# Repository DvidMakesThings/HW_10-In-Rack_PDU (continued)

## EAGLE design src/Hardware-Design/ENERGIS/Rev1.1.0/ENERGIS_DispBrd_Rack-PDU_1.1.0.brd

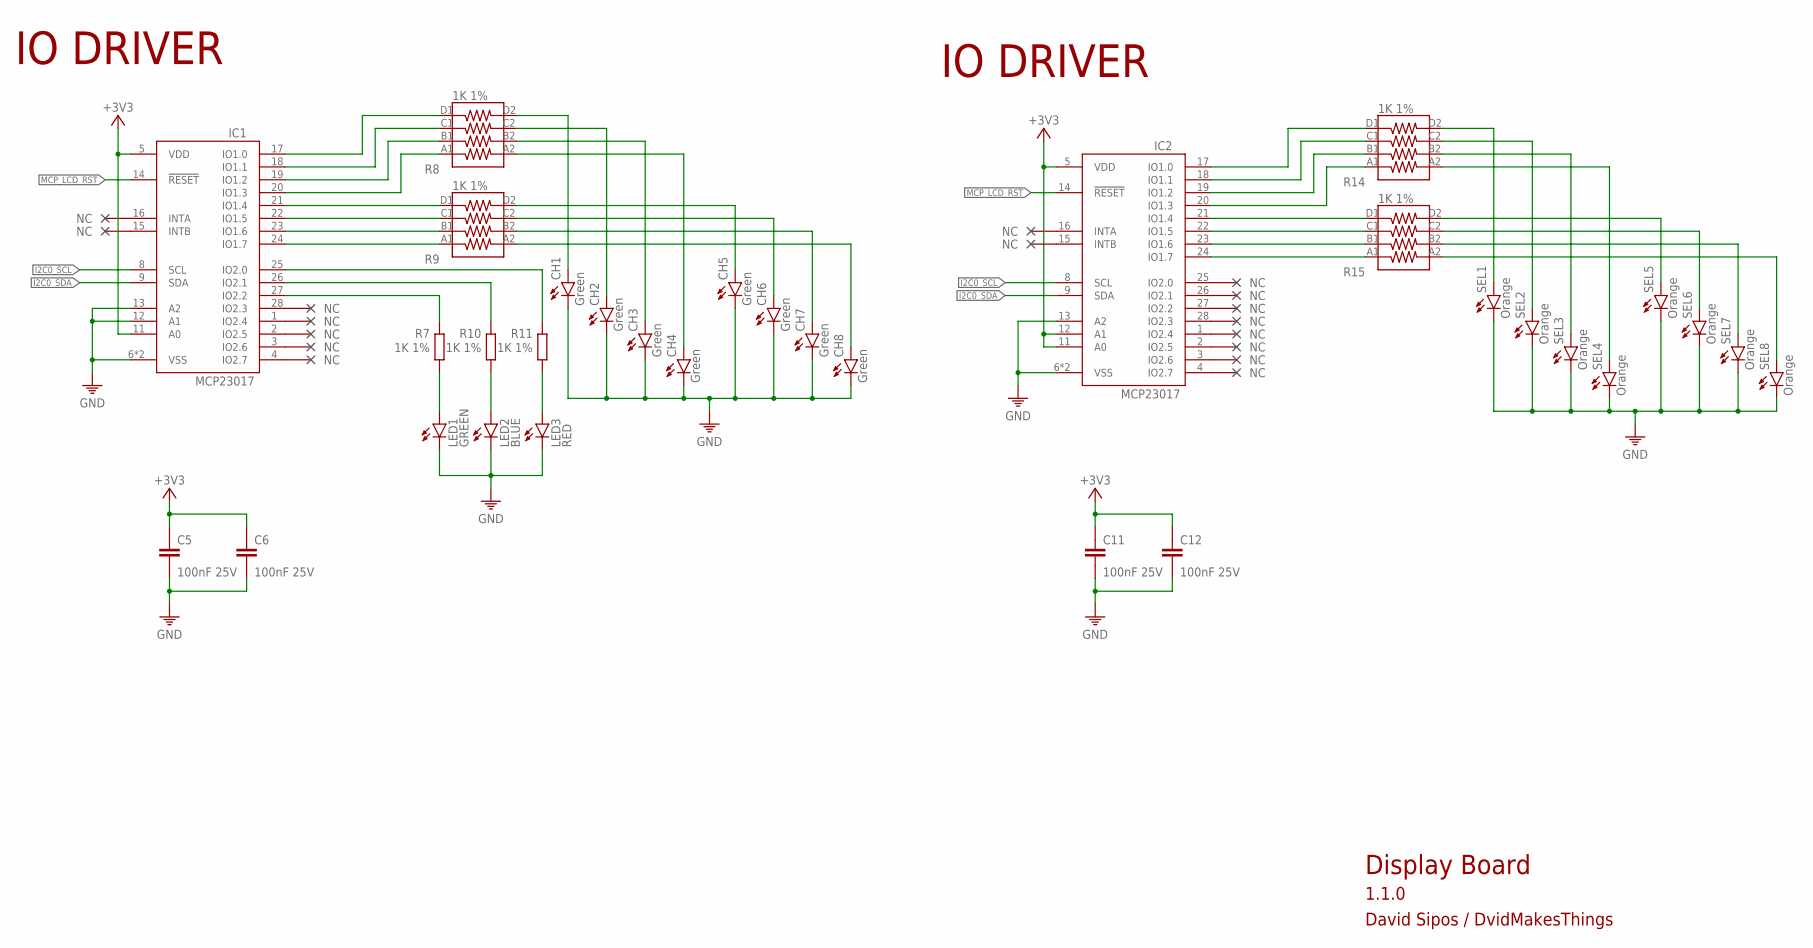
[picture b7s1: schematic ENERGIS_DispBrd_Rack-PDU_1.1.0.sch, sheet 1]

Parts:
C5, C6, C11, C12: 100nF 25V; 0402
CH1, CH2, CH3, CH4, CH5, CH6, CH7, CH8: Green; LED-0805
IC1, IC2: MCP23017T-E/ML; QFN28[6X6]ML
LED1: GREEN; LED3MM
LED2: BLUE; LED3MM
LED3: RED; LED3MM
R7, R10, R11: 1K 1%; 0402
R8, R9, R14, R15: 1K 1%; _0603X4-1206
SEL1, SEL2, SEL3, SEL4, SEL5, SEL6, SEL7, SEL8: Orange; LED-0805

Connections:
+3V3: C5.1, C6.1, C11.1, C12.1, IC1.5 (VDD), IC1.11 (A0), IC2.5 (VDD), IC2.11 (A0), IC2.12 (A1); also elsewhere on the board
GND: C5.2, C6.2, C11.2, C12.2, CH1.C, CH2.C, CH3.C, CH4.C, CH5.C, CH6.C, CH7.C, CH8.C, IC1.6 (VSS), IC1.12 (A1), IC1.13 (A2), IC1.PAD (VSS), IC2.6 (VSS), IC2.13 (A2), IC2.PAD (VSS), LED1.K (C), LED2.K (C), LED3.K (C), SEL1.C, SEL2.C, SEL3.C, SEL4.C, SEL5.C, SEL6.C, SEL7.C, SEL8.C; also elsewhere on the board
I2C0_SCL: IC1.8 (SCL), IC2.8 (SCL); also elsewhere on the board
I2C0_SDA: IC1.9 (SDA), IC2.9 (SDA); also elsewhere on the board
MCP_LCD_RST: IC1.14 (!RESET), IC2.14 (!RESET); also elsewhere on the board
unnamed: IC2.17 (IO1.0), R14.D1 (4)
unnamed: IC2.18 (IO1.1), R14.C1 (3)
unnamed: IC2.19 (IO1.2), R14.B1 (2)
unnamed: IC2.20 (IO1.3), R14.A1 (1)
unnamed: IC2.21 (IO1.4), R15.D1 (4)
unnamed: IC2.22 (IO1.5), R15.C1 (3)
unnamed: IC2.23 (IO1.6), R15.B1 (2)
unnamed: IC2.24 (IO1.7), R15.A1 (1)
unnamed: R14.D2 (5), SEL1.A
unnamed: R14.C2 (6), SEL2.A
unnamed: R14.B2 (7), SEL3.A
unnamed: R14.A2 (8), SEL4.A
unnamed: R15.D2 (5), SEL5.A
unnamed: R15.C2 (6), SEL6.A
unnamed: R15.B2 (7), SEL7.A
unnamed: R15.A2 (8), SEL8.A
unnamed: IC1.26 (IO2.1), R10.1
unnamed: IC1.27 (IO2.2), R7.1
unnamed: IC1.25 (IO2.0), R11.1
unnamed: IC1.17 (IO1.0), R8.D1 (4)
unnamed: IC1.18 (IO1.1), R8.C1 (3)
unnamed: IC1.19 (IO1.2), R8.B1 (2)
unnamed: IC1.20 (IO1.3), R8.A1 (1)
unnamed: IC1.21 (IO1.4), R9.D1 (4)
unnamed: IC1.22 (IO1.5), R9.C1 (3)
unnamed: IC1.23 (IO1.6), R9.B1 (2)
unnamed: IC1.24 (IO1.7), R9.A1 (1)
unnamed: CH1.A, R8.D2 (5)
unnamed: CH2.A, R8.C2 (6)
unnamed: CH3.A, R8.B2 (7)
unnamed: CH4.A, R8.A2 (8)
unnamed: CH5.A, R9.D2 (5)
unnamed: CH6.A, R9.C2 (6)
unnamed: CH7.A, R9.B2 (7)
unnamed: CH8.A, R9.A2 (8)
unnamed: LED3.A, R11.2
unnamed: LED2.A, R10.2
unnamed: LED1.A, R7.2

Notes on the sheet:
IO DRIVER
Display Board
David Sipos / DvidMakesThings

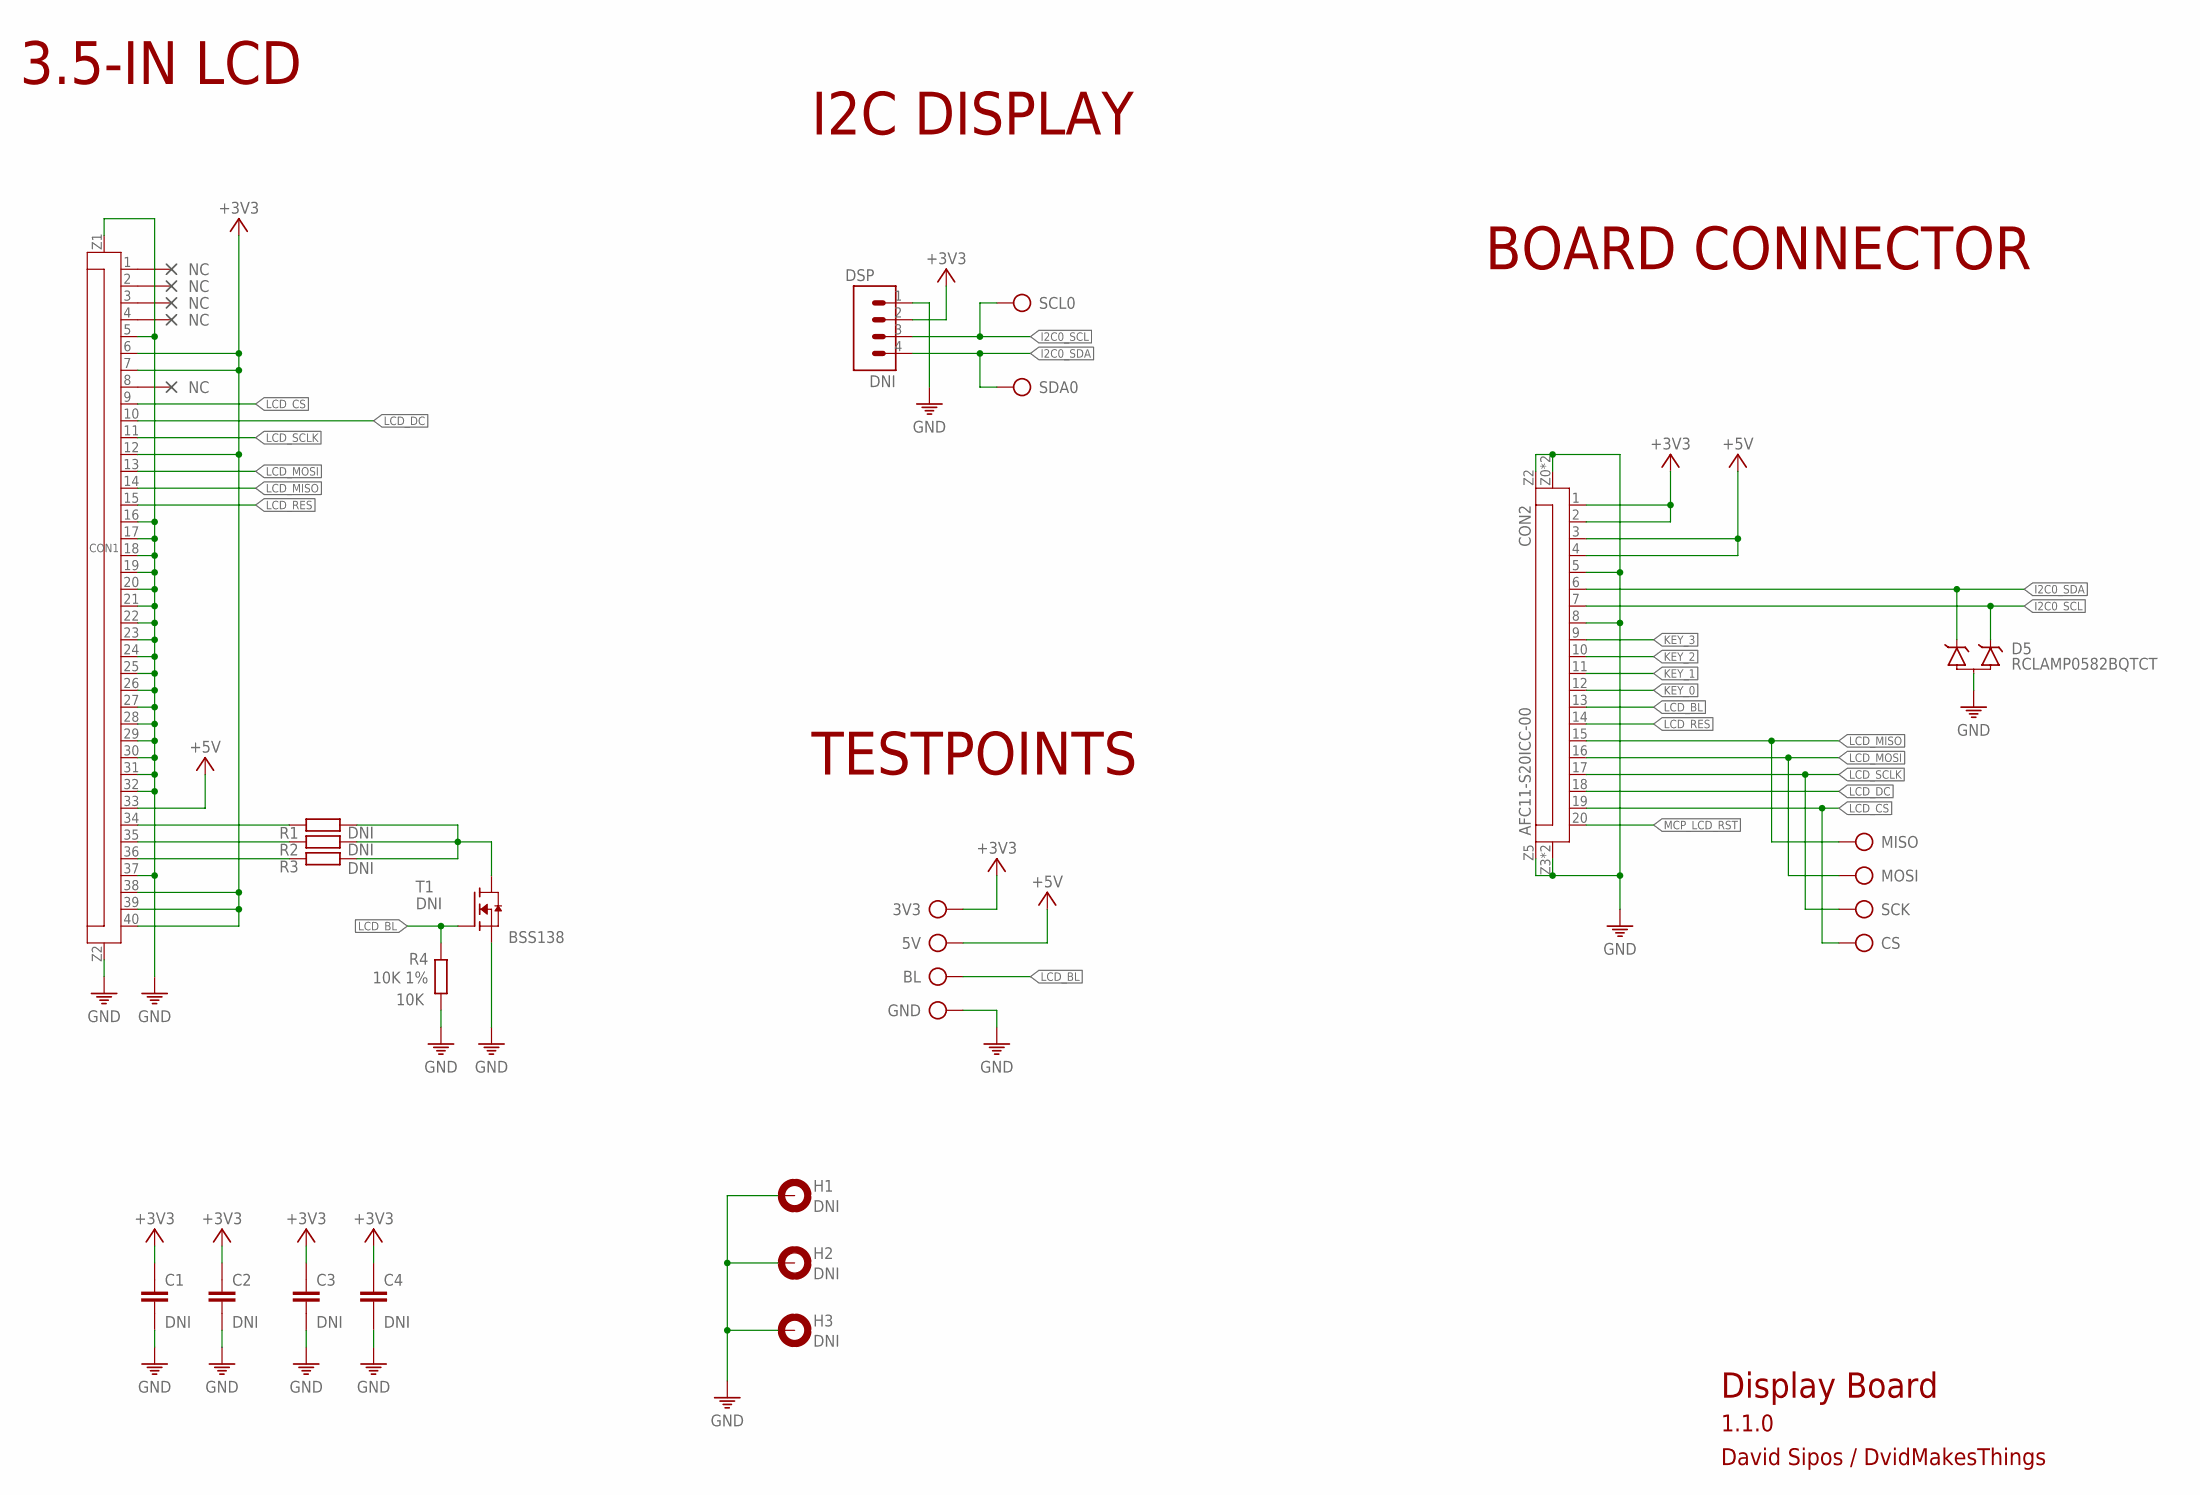
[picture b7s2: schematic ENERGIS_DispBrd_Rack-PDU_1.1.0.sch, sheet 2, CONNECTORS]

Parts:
3V3, 5V: DNI; TP-ROUND
BL: DNI; TP-ROUND
C1, C2, C3, C4: DNI; C0402
CON1: DNI; FPC40_3.5TFT
CON2: AFC11-S20ICC-00; FPC20
CS: DNI; TP-ROUND
D5: RCLAMP0582BQTCT; SC75
DSP: DNI; 1X4
GND: DNI; TP-ROUND
H1, H2, H3: DNI; 3,2-PAD
MISO: DNI; TP-ROUND
MOSI: DNI; TP-ROUND
R1, R2, R3: DNI; 0402
R4: 10K 1%; 0402
SCK: DNI; TP-ROUND
SCL0: DNI; TP-ROUND
SDA0: DNI; TP-ROUND
T1: DNI; SOT23

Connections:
+3V3: 3V3.TP, C1.1, C2.1, C3.1, C4.1, CON1.6, CON1.7, CON1.12, CON1.38, CON1.39, CON1.40, CON2.1, CON2.2, DSP.2; also elsewhere on the board
+5V: 5V.TP, CON1.33, CON2.3, CON2.4
GND: C1.2, C2.2, C3.2, C4.2, CON1.5, CON1.16, CON1.17, CON1.18, CON1.19, CON1.20, CON1.21, CON1.22, CON1.23, CON1.24, CON1.25, CON1.26, CON1.27, CON1.28, CON1.29, CON1.30, CON1.31, CON1.32, CON1.37, CON1.Z1, CON1.Z2, CON2.5, CON2.8, CON2.Z0 (Z1), CON2.Z1, CON2.Z2, CON2.Z3, CON2.Z4 (Z3), CON2.Z5 (Z4), D5.3, DSP.1, GND.TP, H1.B3,2, H2.B3,2, H3.B3,2, R4.2, T1.2 (S); also elsewhere on the board
I2C0_SCL: CON2.7, D5.1, DSP.3, SCL0.TP; also elsewhere on the board
I2C0_SDA: CON2.6, D5.2, DSP.4, SDA0.TP; also elsewhere on the board
KEY_0: CON2.12; also elsewhere on the board
KEY_1: CON2.11; also elsewhere on the board
KEY_2: CON2.10; also elsewhere on the board
KEY_3: CON2.9; also elsewhere on the board
LCD_BL: BL.TP, CON2.13, R4.1, T1.1 (G)
LCD_CS: CON1.9, CON2.19, CS.TP
LCD_DC: CON1.10, CON2.18
LCD_MISO: CON1.14, CON2.15, MISO.TP
LCD_MOSI: CON1.13, CON2.16, MOSI.TP
LCD_RES: CON1.15, CON2.14
LCD_SCLK: CON1.11, CON2.17, SCK.TP
MCP_LCD_RST: CON2.20; also elsewhere on the board
unnamed: CON1.35, R2.2
unnamed: CON1.36, R3.2
unnamed: R1.1, R2.1, R3.1, T1.3 (D)
unnamed: CON1.34, R1.2

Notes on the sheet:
Display Board
David Sipos / DvidMakesThings
3.5-IN LCD
BOARD CONNECTOR
I2C DISPLAY
TESTPOINTS
BSS138
10K

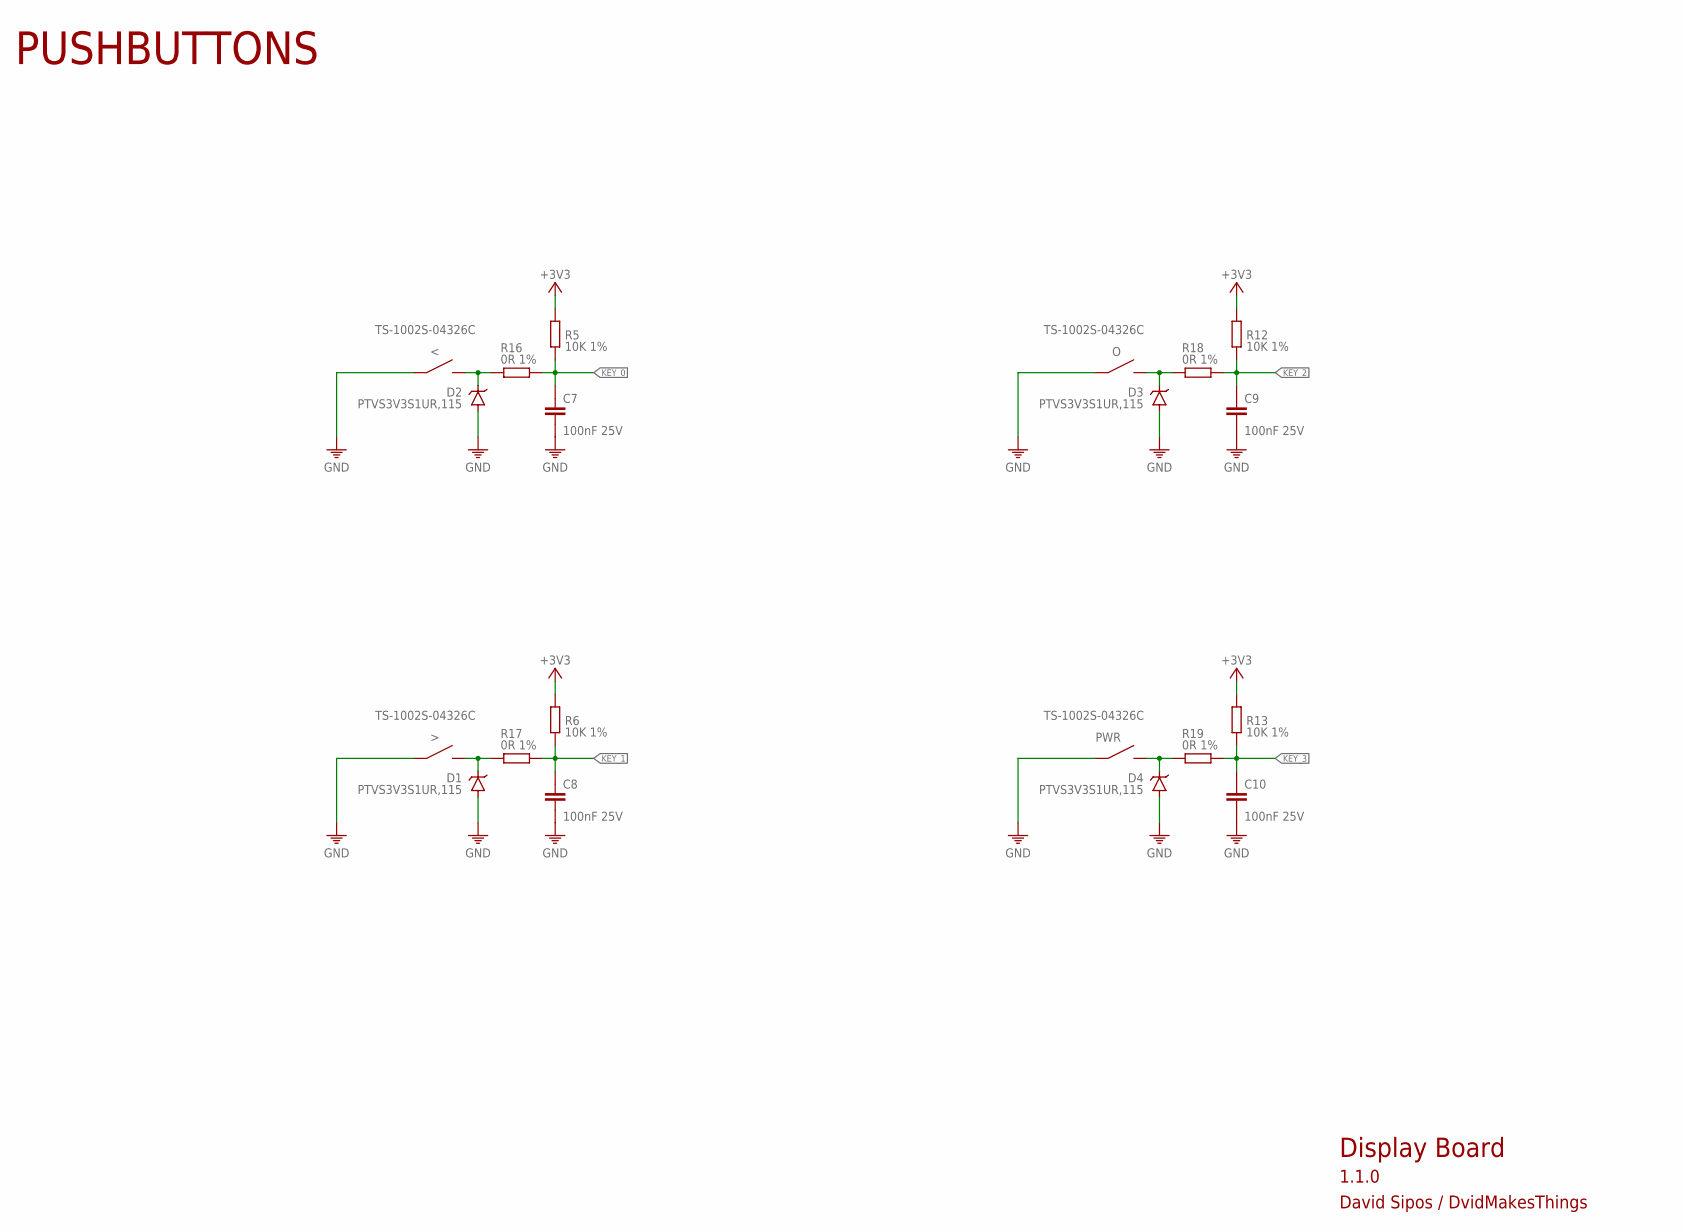
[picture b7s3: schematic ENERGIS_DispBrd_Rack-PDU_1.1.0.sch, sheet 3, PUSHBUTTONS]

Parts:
<: TS-1002S-04326C; PUSHBUTTON-6X6
>: TS-1002S-04326C; PUSHBUTTON-6X6
C7, C8, C9, C10: 100nF 25V; 0402
D1, D2, D3, D4: PTVS3V3S1UR,115; SOD-123
O: TS-1002S-04326C; PUSHBUTTON-6X6
PWR: TS-1002S-04326C; PUSHBUTTON-6X6
R5, R6, R12, R13: 10K 1%; 0402
R16, R17, R18, R19: 0R 1%; 0402

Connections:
+3V3: R5.1, R6.1, R12.1, R13.1; also elsewhere on the board
GND: <.1, <.2, >.1, >.2, C7.2, C8.2, C9.2, C10.2, D1.A, D2.A, D3.A, D4.A, O.1, O.2, PWR.1, PWR.2; also elsewhere on the board
KEY_0: C7.1, R5.2, R16.2; also elsewhere on the board
KEY_1: C8.1, R6.2, R17.2; also elsewhere on the board
KEY_2: C9.1, R12.2, R18.2; also elsewhere on the board
KEY_3: C10.1, R13.2, R19.2; also elsewhere on the board
unnamed: <.3, <.4, D2.C, R16.1
unnamed: D3.C, O.3, O.4, R18.1
unnamed: D4.C, PWR.3, PWR.4, R19.1
unnamed: >.3, >.4, D1.C, R17.1

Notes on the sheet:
Display Board
David Sipos / DvidMakesThings
PUSHBUTTONS

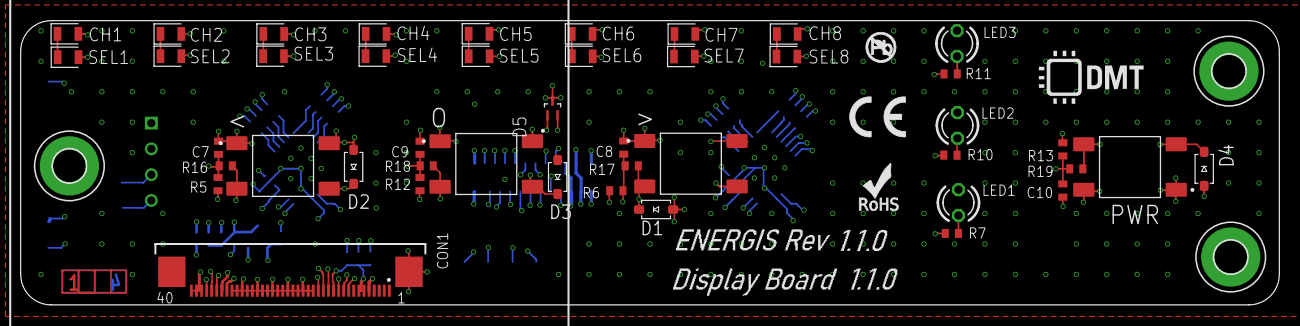
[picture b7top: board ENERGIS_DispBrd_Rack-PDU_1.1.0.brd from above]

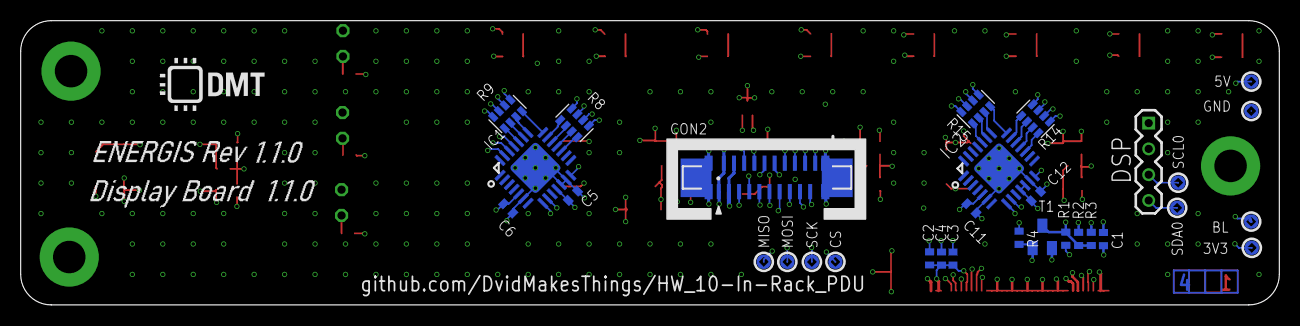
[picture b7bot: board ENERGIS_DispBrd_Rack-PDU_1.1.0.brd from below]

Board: 4 copper layers, 124.0 x 28.0 mm, 83 parts (32 on the bottom side), 63 nets.

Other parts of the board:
U$1, U$5: DNI; DMT
U$8: DNI; CE-4MM
U$9: DNI; ROHS_LOGO_0.18_IN
U$10: DNI; NO_PB_LOGO_0.120

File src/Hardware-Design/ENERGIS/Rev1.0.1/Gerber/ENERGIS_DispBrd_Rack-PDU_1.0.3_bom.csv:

Comment,Designator,Footprint,LCSC Part #
1K 1%,R7,0402,C11702
1K 1%,R8 R9,_0603X4-1206,C110021
1K 1%,R10 R11,0402,C11702
1K 1%,R14 R15,_0603X4-1206,C110021
10K 1%,R4 R5 R6 R12 R13,0402,C25744
100nF 50V,C5 C6 C7 C8 C9 C10 C11 C12,0402,C307331
AFC11-S20ICC-00 ,CON2,FPC20,C11073
BLUE,LED2,LED3MM,C86881
BSS138,T1,SOT23,
DNI,C1 C2 C3 C4,C0402,
DNI,CON1,FPC40_3.5TFT,
DNI,DSP,1X4,
DNI,R1 R2 R3,0402,
GREEN,LED1,LED3MM,C414645
Green,CH1 CH2 CH3 CH4 CH5 CH6 CH7 CH8,LED-0805,C2297
MCP23017T-E/ML ,IC1 IC2,QFN28[6X6]ML,C629439
Orange,SEL1 SEL2 SEL3 SEL4 SEL5 SEL6 SEL7 SEL8,LED-0805,C434437
RED,LED3,LED3MM,C330752
TP,3V3 5V BL CS GND MISO MOSI SCK SCL0 SDA0,TP,
TS-1002S-04326C ,< > O PWR,PUSHBUTTON-6X6,C455108

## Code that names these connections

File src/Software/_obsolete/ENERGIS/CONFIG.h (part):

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/********************************************************************************
 *                        RP2040 GPIO PIN ASSIGNMENTS                           *
 ********************************************************************************/
#define UART0_RX 0
#define UART0_TX 1
#define I2C1_SDA 2
#define I2C1_SCL 3
#define I2C0_SDA 4
#define I2C0_SCL 5
#define LCD_DC 6
#define LCD_BL 7
#define LCD_MISO 8  // spi1 rx
#define LCD_CS 9    // spi1 csn
#define LCD_SCLK 10 // spi1 sck
#define LCD_MOSI 11 // spi1 tx
#define KEY_0 12
#define KEY_1 13
#define KEY_2 14
#define KEY_3 15
#define BUT_PLUS KEY_1
#define BUT_MINUS KEY_0
#define BUT_SET KEY_2
#define BUT_PWR KEY_3
#define W5500_MISO 16
#define W5500_CS 17
#define W5500_SCK 18
#define W5500_MOSI 19
#define W5500_RESET 20
#define W5500_INT 21
#define LCD_RESET 22
#define MCP_REL_RST 23
#define MCP_LCD_RST 24
#define VREG_EN 25
#define ADC_VUSB 26
#define NC 27
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#define ADC_VREF 3.00f
#define ADC_MAX 4096.0f
#define ADC_TOL 1.005f // +0.5% correction factor
#define V_USB 0
#define V_SUPPLY 3
#define TEMP_SENSOR 4

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 *                       MCP23017 RELAY BOARD CONFIGURATIONS                    *
 ********************************************************************************/
#define MCP_RELAY_ADDR 0x20 // 0b0100000
#define REL_0 0
#define REL_1 1
#define REL_2 2
#define REL_3 3
#define REL_4 4
#define REL_5 5
#define REL_6 6
#define REL_7 7
#define MUX_A 8
#define MUX_B 9
#define MUX_C 10
#define MUX_EN 11

/********************************************************************************
 *                        MCP23017 DISPLAY BOARD CONFIGURATIONS                 *
 ********************************************************************************/
#define MCP_DISPLAY_ADDR 0x21 // 0b0100001
#define OUT_1 0
#define OUT_2 1
#define OUT_3 2
#define OUT_4 3
#define OUT_5 4
#define OUT_6 5
#define OUT_7 6
#define OUT_8 7
#define FAULT_LED 8
#define ETH_LED 9
#define PWR_LED 10
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 ********************************************************************************/

#define MCP_SELECTION_ADDR 0x23
#define MCP_SEL_RST MCP_LCD_RST
#define SEL_1 0
#define SEL_2 1
#define SEL_3 2
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#define TX_MUX_6 5
#define TX_MUX_7 6
#define TX_MUX_8 7
#define UART_MUX_Y UART0_TX
#define MUX_SELECT_A MUX_A
#define MUX_SELECT_B MUX_B
#define MUX_SELECT_C MUX_C
#define MUX_ENABLE MUX_EN

// HLW8032 UART Channels via Optocouplers
/********************************************************************************
 *                           HLW8032 UART CHANNELS                              *
 ********************************************************************************/
#define TX_CH1 0
#define TX_CH2 1
#define TX_CH3 2
#define TX_CH4 3
#define TX_CH5 4
#define TX_CH6 5
#define TX_CH7 6
#define TX_CH8 7

/********************************************************************************
 *                         LCD REGISTERS AND CONFIGURATION                      *
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
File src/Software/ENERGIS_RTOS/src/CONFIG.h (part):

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#define HLW8032_FRAME_LENGTH 24
#define NUM_CHANNELS 8
#define POLL_INTERVAL_MS 6000u
#define TX_CH1 0
#define TX_CH2 1
#define TX_CH3 2
#define TX_CH4 3
#define TX_CH5 4
#define TX_CH6 5
#define TX_CH7 6
#define TX_CH8 7
/** @} */

/********************************************************************************
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/** @name GPIO Assignments
 * @ingroup config01
 * @{ */
#define UART0_RX 0
#define UART0_TX 1
#define I2C1_SDA 2
#define I2C1_SCL 3
#define I2C0_SDA 4
#define I2C0_SCL 5
#define GPIO6 6   // Not used anymore
#define GPIO7 7   // Not used anymore
#define GPIO8 8   // Not used anymore
#define GPIO9 9   // Not used anymore
#define GPIO10 10 // Not used anymore
#define GPIO11 11 // Not used anymore
#define KEY_0 12
#define KEY_1 13
#define KEY_2 14
#define KEY_3 15
#define BUT_PLUS KEY_1
#define BUT_MINUS KEY_0
#define BUT_SET KEY_2
#define BUT_PWR KEY_3
#define W5500_MISO 16
#define W5500_CS 17
#define W5500_SCK 18
#define W5500_MOSI 19
#define W5500_RESET 20
#define W5500_INT 21
#define FAN_CTRL 22 // Fan control (not used)
#define MCP_MB_RST 23
#define MCP_DP_RST 24
#define VREG_EN 25
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#define ADC_VREF 3.0f
#define ADC_MAX 4096.0f
#define ADC_TOL 1.005f // +0.5% correction factor
#define V_USB 0
#define V_SUPPLY 3
#define TEMP_SENSOR 4
#define VBUS_DIVIDER 2.0f
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 * @ingroup config01
 * @{ */
#define MCP_RELAY_ADDR 0x20 // 0b0100000
#define REL_0 0
#define REL_1 1
#define REL_2 2
#define REL_3 3
#define REL_4 4
#define REL_5 5
#define REL_6 6
#define REL_7 7
#define MUX_A 8
#define MUX_B 9
#define MUX_C 10
#define MUX_EN 11
/** @} */

/********************************************************************************
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 * @ingroup config01
 * @{ */
#define MCP_DISPLAY_ADDR 0x21 // 0b0100001
#define OUT_1 0
#define OUT_2 1
#define OUT_3 2
#define OUT_4 3
#define OUT_5 4
#define OUT_6 5
#define OUT_7 6
#define OUT_8 7
#define FAULT_LED 8
#define ETH_LED 9
#define PWR_LED 10
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
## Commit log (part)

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2025-01-28 add datasheets
2025-01-29 upload PCB design
2025-01-30 start Relay board design
2025-01-30 add readme
2025-01-31 add SMPS to relay board
2025-01-31 finish relay board design
2025-01-31 add pictures
2025-01-31 first order send to JLCPCB
2025-01-31 Calculate costs, add Farnell, DigiKey BOM for missing parts
2025-02-01 generate Gerber files
2025-02-01 designing case
2025-02-01 finalize enclosure
2025-02-02 change X1, X2 because of shortage
2025-02-02 Update README.md - Changed number of relays on the relay board
    If I'm not completely wrong I see 8 instead of 6 relays on the relay board.
2025-02-02 Update README.md - Corrected the name of the link of the relay board 3D view
2025-02-02 update documentation
2025-02-02 changed track with at relay output. Handles 15A max now
2025-02-02 add process visualisation
2025-02-02 Fix design typo in README.md
2025-02-02 Align MD table and non-coplanar spelling in README.md
2025-02-02 Dev Phases (Markdown) table alignment in README.md
    Minor, but later editors to the Dev Phases table might appreciate it, hehe
2025-02-03 Some Markdown linting in README.md
2025-02-03 add funding options
2025-02-03 add enclosure design to src
2025-02-03 correct wrong divider resistor values
2025-02-03 export enclosure files
2025-02-04 update order
2025-02-04 add 3D model for for bambu printer
2025-02-06 update status
2025-02-10 add DiffPairCheck to repo. Update Controller-boart to rev1.1
2025-02-16 start working on rev2.0
2025-02-18 start Displayboard rev 2
2025-02-20 working on Rev2.0
2025-02-22 finished with design update for 2.0
2025-02-23 finished Rev2
2025-02-23 add datasheets for Rev2.0
2025-03-03 add circuit description
2025-03-03 clear repo
2025-03-04 source code - pre version. Never RP2040 or any RP series ever. Copiling to this is nightmare
2025-03-06 correct findings
2025-03-07 I2C, SPI-DMA, EEPROM driver ready
2025-03-07 display is fully funcitonal
2025-03-10 add w5500 test
2025-03-11 never again W5500...
2025-03-11 finally a socket open...
2025-03-15 http site is finally working, filled with dummies :D
2025-03-16 add button driver and core task files; remove dummy EEPROM and update configurations
2025-03-18 implementing snmp
2025-03-18 Creating HW release version ENERGIS Rev1.0.0 from CB1.0.21, DB1.0.30, RB1.0.21
2025-05-14 Major PCB update: - Relay board combined with Controller board - SW update not possible via software-boot mode due to CDC-UART conflict: Added FT232 with USB multiplexer: Auto USB path selector - Upd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
2025-05-17 Add UART commands and imlement SNMP functionality
2025-05-17 Clean source code, delete obsolete functions
2025-05-18 pico system crashed, new programming method to upload. Added overclock to 200MHz@1.15V
2025-05-19 working control page on HTML side
2025-05-20 semi-working settings page on HTML side
2025-05-22 update schematics
2025-05-22 update DspBoard
2025-05-22 update main board
2025-05-22 update BOM
2025-05-23 Working settings page
2025-05-23 refactoring code
2025-05-23 implement HLW8032_driver
2025-05-24 fix HLW8032 driver
2025-05-24 bugfix for CH1 readings issue. Add screen update
2025-05-27 Major PCB update
2025-06-06 starting with documentation
2025-06-10 update design to final state
2025-06-23 update readme with 3D render
2025-08-21 update software, bugfix
2025-08-21 refactor MCP23017 relay driver for race-free operation and add new API functions
2025-08-21 update code with doxygen style documentation
2025-09-05 Baseline commit. Device is functioning as expected, software is working
2025-09-05 update io page
2025-09-06 update files, schematics, images etc
2025-09-06 update enclosure design
2025-09-06 continue debugging
2025-09-08 Update licensing to protect hardware components
2025-09-09 testing ethernet
2025-09-14 Add software ESD protection to button control and port expanders. Design sheet metal shielding around electronics. Add ethernet test
2025-09-14 add readme to shielding
2025-09-14 add ethernet test
2025-09-15 re-run tests due to UTFW change
2025-09-17 add tests with detailed logging
2025-09-19 add pcap tests. Small fixes
2025-09-20 adapt design to NextPCB dru
2025-09-24 update component library to NextPCB
2025-09-25 add 3D rendering
2025-09-26 generate RoHS comliance
2025-09-26 generate PCB reports
2025-09-26 generate Gerber
2025-09-26 export Gerbers
2025-09-28 add price calculation
2025-09-28 update repo
2025-09-28 update pricecalc
2025-09-28 add 3D parts
2025-09-29 update Gerbers
2025-10-04 update snmp with new OIDs
2025-10-05 continue with testing. Added regression
2025-10-23 ICT-footprint
2025-11-06 general update for the repo
2025-11-09 Major update - RTOS migration
2025-11-10 Add HealthTask to RTOS
2025-11-10 bugfix for RTOS tasks
2025-11-10 first fully functional bugfree??? build yeey
2025-11-11 update code documentation
2025-11-11 create RTOS documentation
2025-11-11 create automation manual
2025-11-12 add mac calculation
2025-11-14 refactoring storageTask
2025-11-14 push changes
2025-11-15 add metrics
2025-11-15 add metrics.txt
2025-11-15 update metrics
2025-11-16 fix watchdog reset during EE dump
2025-11-16 add user Manual
2025-11-17 Fiexed: EEPROM dump causes WDT reset: using pointer arithmetic instead of strncat Added: Power down mode now supported
2025-11-17 update manual with the new behaviour
2025-11-18 update web ui
2025-11-18 add gzip
2025-11-18 implement help.html as gzip
2025-11-18 prepare event log for error logging
2025-11-18 prepare for adding error logger
2025-11-18 Normalize line endings
2025-11-19 implement failure memory
2025-11-25 major pre-release update on project files and documentation
2025-11-25 add documentation
2025-12-01 correct BOM
2025-12-10 clear documentation, software bugfix
2025-12-11 implement OverCurrent Protection
2025-12-12 update documentation, bugfix
2025-12-17 add documentation, implement provisioning
2025-12-19 add linux compatibility
2026-01-01 code update and bugfix
2026-01-01 add channel labeling feature
2026-01-02 add preset feature, add apply-on-startup feature, minor fixes
2026-01-02 sleep mode bugfix: NIC not initialized after power down, when the network link is down
2026-01-02 add more digits in UI current and power data
2026-01-03 bugfix: network changes not persisted when changed in UI
2026-01-13 bugfix
2026-01-18 update readme, minor bugfix
